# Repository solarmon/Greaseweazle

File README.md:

# Greaseweazle Projects
Greaseweazle Projects

Various PCB projects based on **keirf**'s Greaseweazle project for reading and writing floppy disks:

https://github.com/keirf/Greaseweazle

Special thanks to **Stefano Cappelli** of https://www.picoelements.com/ for making the time and effort to beta testing these boards. 

# Greaseweazle F1 Plus

## Features

These are the features of the GW F1 Plus boards.

**Standard Features:**
|   | F1 Plus Mini Rev 1.1 | F1 Plus  Rev 1.1 | F1 Plus Gotek	 Rev 1.1 | F1 Plus 3.5" Rev 1.1 |
|---|---|---|---|---|
|Jumperless Update|Yes|Yes|Yes|Yes|
|Multiple Drives|Yes|Yes|Yes|Yes|
|Write-Protect Jumper| - |Yes|Yes|Yes|
|Buffered Outputs| - |Yes|Yes|Yes|
|High-Speed USB| - | - | - | - |			
|12v Power| - |Yes|Yes|Yes|
|Flippy Drive| - |Yes|Yes|Yes|
|Disk Change Detect|Yes|Yes|Yes|Yes|
|User Outputs|3|3|3|3|

Note: **Disk Change Detect** allows WinUAE integration - see https://amiga.robsmithdev.co.uk/winuae

The features of the official Greaseweazle models can be seen at:

https://github.com/keirf/Greaseweazle/wiki/Greaseweazle-Models

**Other Features:**
|   | F1 Plus Mini Rev 1.1 | F1 Plus  Rev 1.1 | F1 Plus Gotek	 Rev 1.1 | F1 Plus 3.5" Rev 1.1 |
|---|---|---|---|---|
|Gotek Case Form Factor| - | -  |Yes|		-		|
|3.5" Floppy Drive Form Factor| - | - |		-		|			Yes|
|STM32 Blue Pill MCU|Yes|Yes|Yes|Yes|
|**Arduino Nano Track Display:**| - | - |		Yes|				Yes|
|	- LEDC68 Display| - | - |			Yes|				Yes|
|	- 0.91" OLED Display| - | - |		(Yes)|			Yes|
|	- 0.96" OLED Display| - | - |		(Yes)|			Yes|
|	- SD Card Reader| - | - |			Yes|				Yes|
|USB ESD Protection| - | (Yes) |				Yes|				Yes|
|12V Reverse Polarity Protection| - | Yes |	Yes|				Yes|
|Poly Fuse| - |Yes|						Yes|				Yes|
|**LED Status:**|Yes|Yes|						Yes|				Yes|
|	- Activity|Yes|Yes|					Yes|				Yes|
|	- 3.3V|Yes|Yes|						Yes|				Yes|
|	- 5V|Yes|Yes|							Yes|				Yes|
|	- 12V| - |Yes |							Yes|				Yes|
| - Type: SMT|Yes|Yes| - | Yes|
| - Type: THT|Yes|Yes| Yes | Yes|
|**Power Jumpers:**|Yes|Yes|						Yes|				Yes|
|	- 12V|-|Yes|Yes|Yes|
|	- 5V|Yes|Yes|Yes|Yes|
|Write Enable Jumper| - |Yes|				Yes|				Yes|
|Input pullups|Yes|Yes|					Yes|				Yes|
|Reset Button|Yes|Yes|					Yes|				Yes|
|Serial Programming Header|Yes|Yes|		Yes|				Yes|
|SWD Programming Header|-|Yes|			Yes|				Yes|
|Disk Change Jumper|Yes|Yes|Yes|Yes|

**Note:** The **Disk Change Jumper** allows you to use an Amiga drive with WinUAE.

## Greaseweazle F1 Plus Mini Rev 1.1

**Design Files:** https://github.com/solarmon/Greaseweazle/tree/main/Greaseweazle%20F1%20Plus%20Mini%20Rev%201.1

This is the most basic F1 Plus model and has the smallest footprint.

## Greaseweazle F1 Plus Rev 1.1

**Design Files:** https://github.com/solarmon/Greaseweazle/tree/main/Greaseweazle%20F1%20Plus%20Rev%201.1

This is the standard F1 Plus model, has a standard footprint but no Track Display features. 

## Greaseweazle F1 Plus Gotek

**Design Files:** https://github.com/solarmon/Greaseweazle/tree/main/Greaseweazle%20F1%20Plus%20Gotek%20Rev%201.1

This Greaseweazle board has been designed to re-purpose and fit into an original Gotek case; and to make use of its LEDC68 display as a track display.

It has been designed to sit on top of the floppy drive that is connected to it.

## Greaseweazle F1 Plus 3.5"

**Design Files:** https://github.com/solarmon/Greaseweazle/tree/main/Greaseweazle%20F1%20Plus%203.5%20Rev%201.1

This Greaseweazle board has been designed to have a 3.5" floppy drive mounted directly on top of it, using the floppy drive standard mounting holes.

The track display feature can support the LEDC68 Gotek LED display, or a 128x32 0.91" OLED display, or a 128x64 0.96" OLED display.

## Track Display

The GW F1 Plus Gotek/3.5" Track Display is provided by an Arduino Nano. The Arduino sketch for this can be found at:

https://github.com/solarmon/Greaseweazle/tree/main/Arduino_Nano_GW_F1_Plus_Floppy_Drive_Track_Display_LED_and_OLED

The LEDC68 and OLED display adapter board, used in the GW F1 3.5" and GW F1 Plus 3.5" boards, can be found at:

https://github.com/solarmon/Greaseweazle/tree/main/LEDC68%20and%200.9%20Inch%20OLED%20Adapter

# Older Revisions

Design files for older revisions of the GW F1 boards can be found at:

## GW F1 Plus Mini

* Rev 1: https://github.com/solarmon/Greaseweazle/tree/main/Greaseweazle%20F1%20Plus%20Mini
 
## GW F1 Plus

* Rev 1: https://github.com/solarmon/Greaseweazle/tree/main/Greaseweazle%20F1%20Plus

## GW F1 Plus Gotek

* Rev 1: https://github.com/solarmon/Greaseweazle/tree/main/Greaseweazle%20F1%20Plus%20Gotek

## GW F1 Plus 3.5"

* Rev 1: https://github.com/solarmon/Greaseweazle/tree/main/Greaseweazle%20F1%20Plus%203.5

## GW F1 Gotek

* Rev 1 (USB-B): https://github.com/solarmon/Greaseweazle/tree/main/Greaseweazle%20F1%20in%20a%20Gotek%20Case%20(%2B%20USB%20B)
* Rev 1 (USB-A): https://github.com/solarmon/Greaseweazle/tree/main/Greaseweazle%20F1%20in%20a%20Gotek%20Case%20(USB-A)
* Rev 2: https://github.com/solarmon/Greaseweazle/tree/main/Greaseweazle%20F1%20Gotek%20Rev%202
* Rev 2B: https://github.com/solarmon/Greaseweazle/tree/main/Greaseweazle%20F1%20Gotek%20Rev%202B

## GW F1 3.5"

* Rev 1: https://github.com/solarmon/Greaseweazle/tree/main/Greaseweazle%20F1%203.5%20Inch
* Rev 2: https://github.com/solarmon/Greaseweazle/tree/main/Greaseweazle%20F1%203.5%20Inch%20Rev%202
* Rev 2B: https://github.com/solarmon/Greaseweazle/tree/main/Greaseweazle%20F1%203.5%20Inch%20Rev%202B

## Track Display

These older revision GW F1 Plus Track Display is provided by an Arduino Nano. The Arduino sketch for this can be found at:

https://github.com/solarmon/Greaseweazle/tree/main/Arduino_Nano_GW_F1_Floppy_Drive_Track_Display_LED_and_OLED_v1

The LEDC68 and OLED display adapter board can be found at:

https://github.com/solarmon/Greaseweazle/tree/main/LEDC68%20and%200.9%20Inch%20OLED%20Adapter

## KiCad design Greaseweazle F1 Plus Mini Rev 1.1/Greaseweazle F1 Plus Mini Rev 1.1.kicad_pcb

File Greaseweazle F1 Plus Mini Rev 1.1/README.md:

# Greaseweazle F1 Plus Mini

This is the most basic F1 Plus model and has the smallest footprint.

## Jumpers

* **JP101** - Disk Change
  - **Pin 34** (Default) - For PC drives
  - **Pin 2** - For Amiga drives

* **JP102** - Join S0/B
  - If **JP101** set to **Pin 2** then set JP102 to join S0 with B

To use an **Amiga** floppy drive with WinUAE, jumper **JP101** to **Pin 2** and jumper **JP102**. An Amiga drive set to S0 will be usable in WinuAE as drive B.

## Headers

* **JP5** - Reset

* **CN4** - USB Header

* **CN5** - Serial Port

* **DH2** - +5V LED
* **DH3** - +3V3 LED
* **DH4** - ACT LED

## Connectors

* **CN1** - Floppy Data
* **CN2** - Floppy Power (Out)
* **CN3** - USB B
* **CN6** - Floppy Power (In)

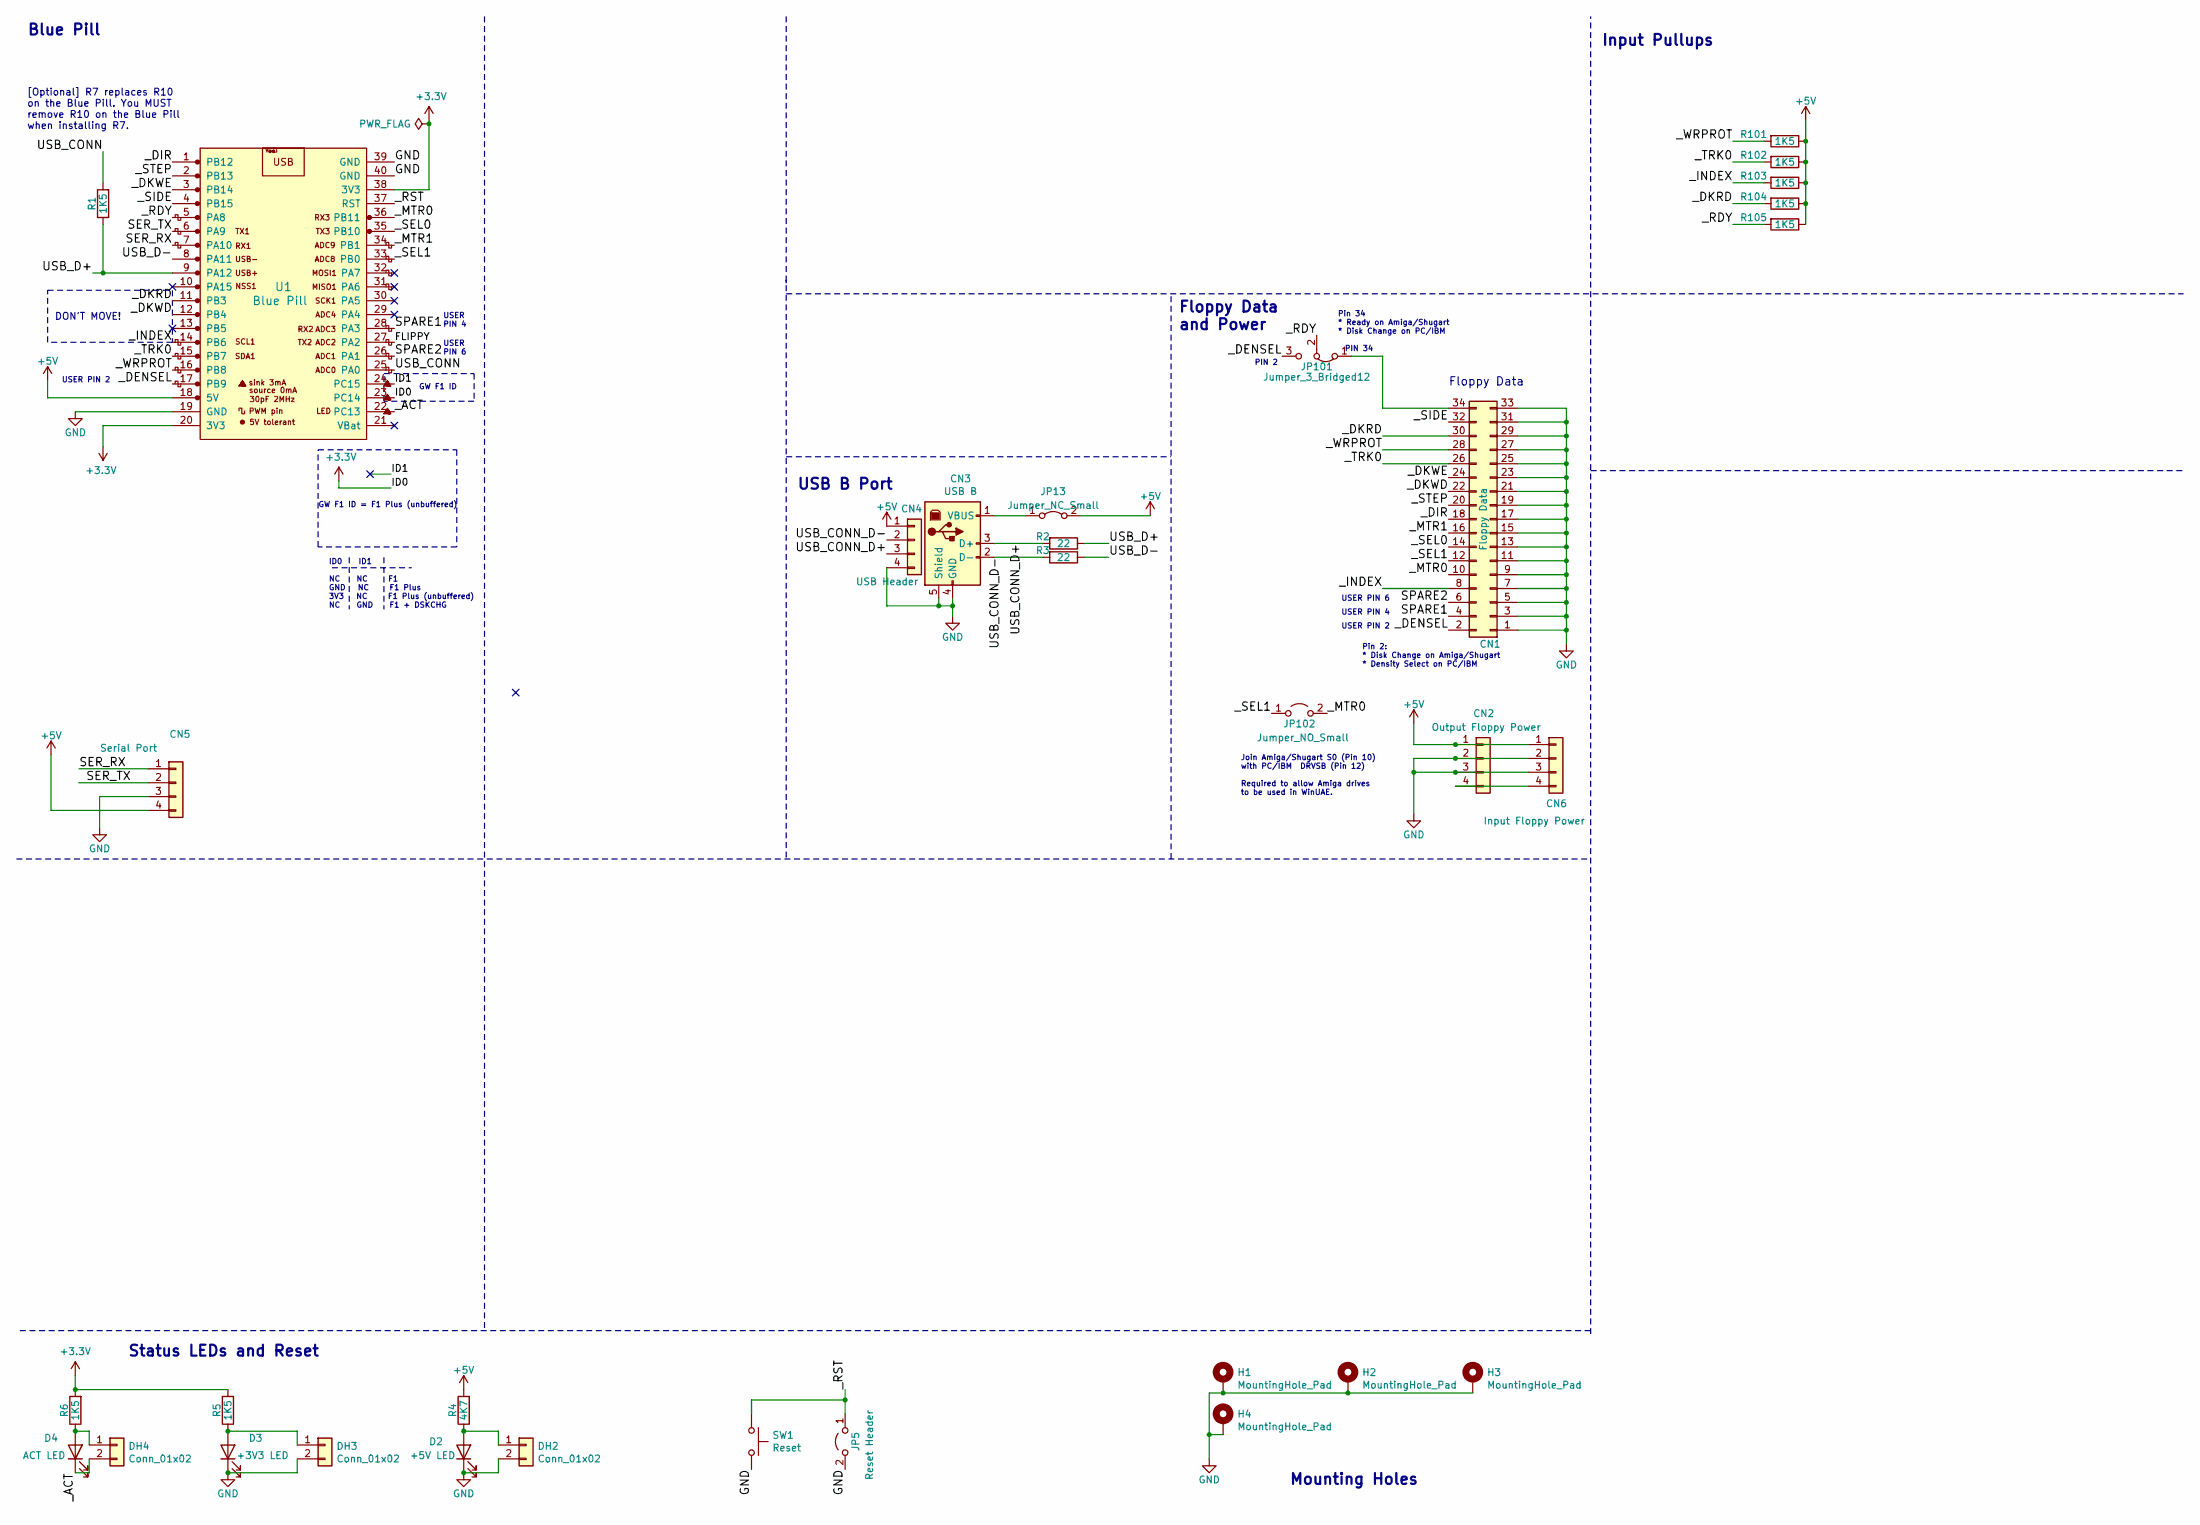
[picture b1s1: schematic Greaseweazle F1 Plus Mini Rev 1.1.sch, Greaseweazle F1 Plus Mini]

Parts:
CN1: Floppy Data; PinHeader_2x17_P2.54mm_Vertical
CN2: Output Floppy Power; PinHeader_1x04_P2.54mm_Horizontal
CN3: USB B; conn_usb_B; LCSC C498173
CN4: USB Header; PinHeader_1x04_P2.54mm_Vertical
CN5: Serial Port; PinHeader_1x04_P2.54mm_Vertical
CN6: Input Floppy Power; PinHeader_1x04_P2.54mm_Vertical
D2: +5V LED; LED_0805_2012Metric_Pad1.15x1.40mm_HandSolder
D3: +3V3 LED; LED_0805_2012Metric_Pad1.15x1.40mm_HandSolder
D4: ACT LED; LED_0805_2012Metric_Pad1.15x1.40mm_HandSolder
DH2, DH3, DH4: Conn_01x02; PinHeader_1x02_P2.54mm_Vertical
H1, H2, H3, H4: MountingHole_Pad; HOLE_3MM
JP5: Reset Header; PinHeader_1x02_P2.54mm_Vertical
JP13: Jumper_NC_Small; PinHeader_1x02_P2.54mm_Vertical
JP101: Jumper_3_Bridged12; PinHeader_1x03_P2.54mm_Vertical
JP102: Jumper_NO_Small; PinHeader_1x02_P2.54mm_Vertical
R1, R101, R102, R103, R104, R105: 1K5; R_0805_2012Metric
R2, R3: 22; R_0805_2012Metric
R4: 4K7; R_0805_2012Metric_Pad1.20x1.40mm_HandSolder
R5, R6: 1K5; R_0805_2012Metric_Pad1.20x1.40mm_HandSolder
SW1: Reset; SW_Tactile_SPST_Angled_PTS645Vx83-2LFS
U1: Blue Pill; YAAJ_BluePill_1

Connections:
+3V3: R5.2, R6.2, U1.20 (3V3), U1.23 (PC14), U1.38 (3V3)
+5V: CN2.1, CN4.1, CN5.4, CN6.1, JP13.2 (B), R4.2, R101.1, R102.1, R103.1, R104.1, R105.1, U1.18 (5V)
/FLIPPY: U1.27 (PA2)
/ID1: U1.24 (PC15)
/SER_RX: CN5.1, U1.7 (PA10)
/SER_TX: CN5.2, U1.6 (PA9)
/SPARE1: CN1.4, U1.28 (PA3)
/SPARE2: CN1.6, U1.26 (PA1)
/USB_CONN: R1.2, U1.25 (PA0)
/USB_CONN_D+: CN3.3 (D+), CN4.3, R2.2
/USB_CONN_D-: CN3.2 (D-), CN4.2, R3.2
/USB_D+: R1.1, R2.1, U1.9 (PA12)
/USB_D-: R3.1, U1.8 (PA11)
/_ACT: D4.1 (K), DH4.2, U1.22 (PC13)
/_DENSEL: CN1.2, JP101.3 (B), U1.17 (PB9)
/_DIR: CN1.18, U1.1 (PB12)
/_DKRD: CN1.30, R104.2, U1.11 (PB3)
/_DKWD: CN1.22, U1.12 (PB4)
/_DKWE: CN1.24, U1.3 (PB14)
/_INDEX: CN1.8, R103.2, U1.14 (PB6)
/_MTR0: CN1.10, JP102.2 (B), U1.36 (PB11)
/_MTR1: CN1.16, U1.34 (PB1)
/_RDY: JP101.2 (C), R105.2, U1.5 (PA8)
/_RST: JP5.1 (A), SW1.1, U1.37 (RST)
/_SEL0: CN1.14, U1.35 (PB10)
/_SEL1: CN1.12, JP102.1 (A), U1.33 (PB0)
/_SIDE: CN1.32, U1.4 (PB15)
/_STEP: CN1.20, U1.2 (PB13)
/_TRK0: CN1.26, R102.2, U1.15 (PB7)
/_WRPROT: CN1.28, R101.2, U1.16 (PB8)
GND: CN1.1, CN1.3, CN1.5, CN1.7, CN1.9, CN1.11, CN1.13, CN1.15, CN1.17, CN1.19, CN1.21, CN1.23, CN1.25, CN1.27, CN1.29, CN1.31, CN1.33, CN2.2, CN2.3, CN3.4 (GND), CN3.5 (Shield), CN4.4, CN5.3, CN6.2, CN6.3, D2.1 (K), D3.1 (K), DH2.2, DH3.2, H1.1, H2.1, H3.1, H4.1, JP5.2 (B), SW1.2, U1.19 (GND), U1.39 (GND), U1.40 (GND)
unnamed: CN1.34, JP101.1 (A)
unnamed: CN2.4, CN6.4
unnamed: CN3.1 (VBUS), JP13.1 (A)
unnamed: D2.2 (A), DH2.1, R4.1
unnamed: D3.2 (A), DH3.1, R5.1
unnamed: D4.2 (A), DH4.1, R6.1

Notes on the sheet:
Floppy Data
[Optional] R7 replaces R10 on the Blue Pill. You MUST remove R10 on the Blue Pill when installing R7.
USB B Port
Floppy Data and Power
Blue Pill
Status LEDs and Reset
Mounting Holes
GW F1 ID = F1 Plus (unbuffered)
GW F1 ID
DON'T MOVE!
Input Pullups
USER PIN 2
USER PIN 4
USER PIN 6
USER PIN 4
USER PIN 6
Pin 34 * Ready on Amiga/Shugart * Disk Change on PC/IBM
ID0 ID1 NC NC F1 GND NC F1 Plus 3V3 NC F1 Plus (unbuffered) NC GND F1 + DSKCHG
Pin 2: * Disk Change on Amiga/Shugart * Density Select on PC/IBM
Join Amiga/Shugart S0 (Pin 10) with PC/IBM DRVSB (Pin 12) Required to allow Amiga drives to be used in WinUAE.
PIN 2
PIN 34

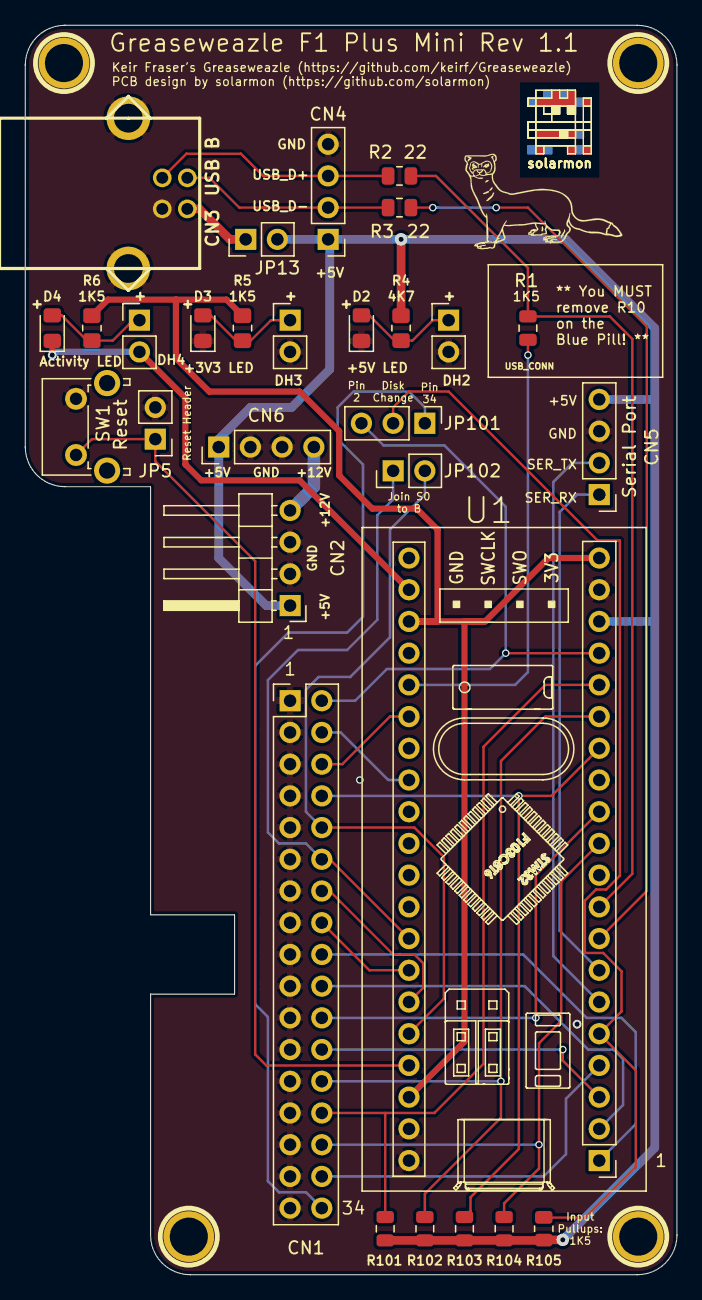
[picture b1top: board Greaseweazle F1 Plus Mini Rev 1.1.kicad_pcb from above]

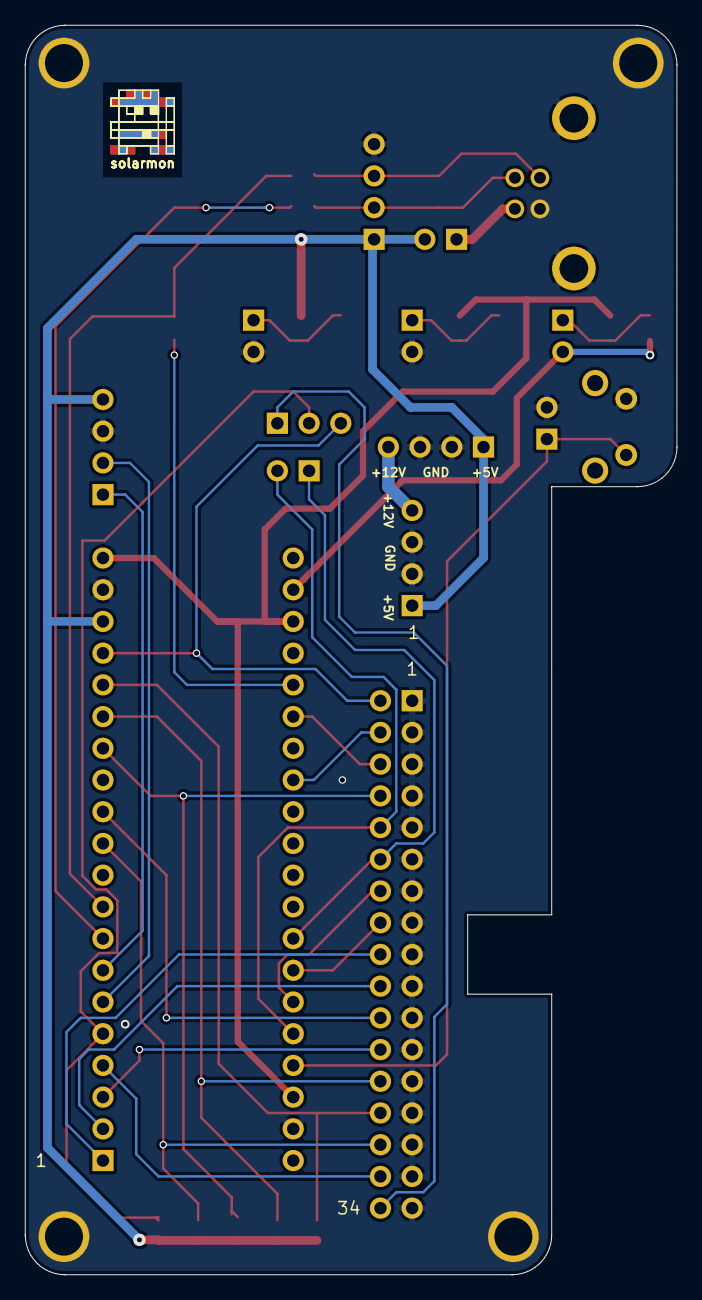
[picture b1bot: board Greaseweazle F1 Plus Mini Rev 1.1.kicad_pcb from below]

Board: 2 copper layers, 52.2 x 100.1 mm, 38 parts (2 on the bottom side), 35 nets.

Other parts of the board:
G**: Weasle; WeasleLogo
solarmon: solarmon-logo-25mils
solarmon#2, solarmon#3, solarmon#4: solarmon-logo-25mils

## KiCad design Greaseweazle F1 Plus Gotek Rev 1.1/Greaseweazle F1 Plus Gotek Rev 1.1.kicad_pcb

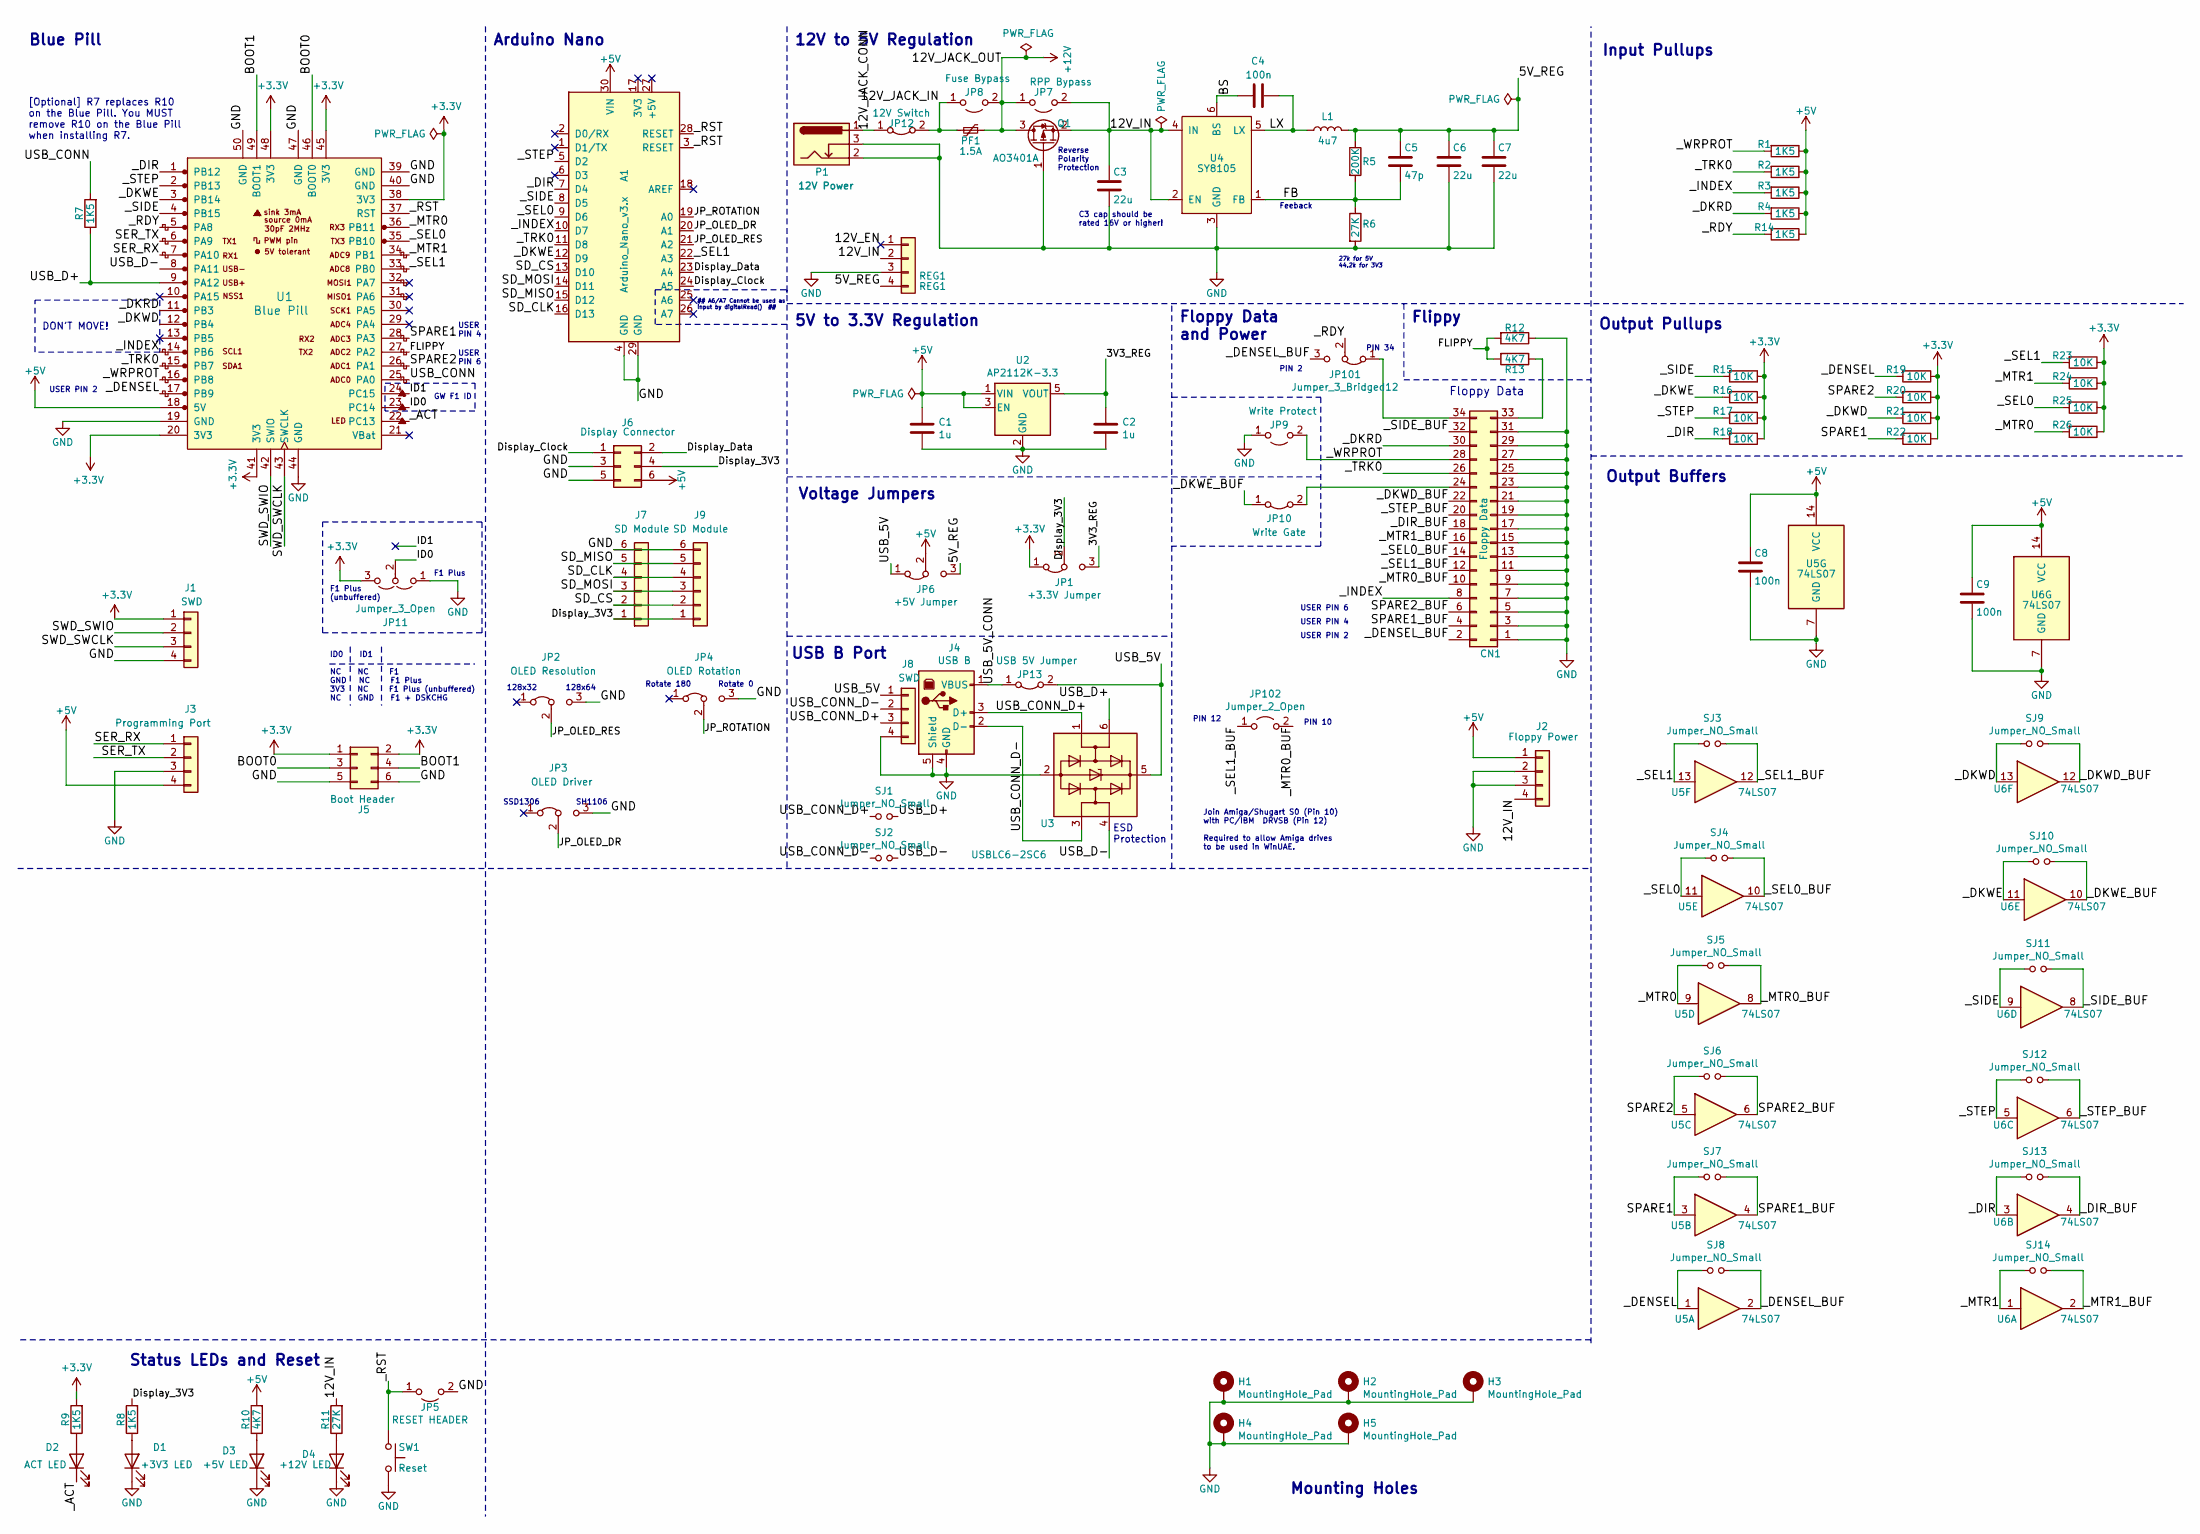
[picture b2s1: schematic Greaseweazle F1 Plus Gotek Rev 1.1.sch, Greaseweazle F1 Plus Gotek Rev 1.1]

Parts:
A1: Arduino_Nano_v3.x; Arduino_Nano
C1, C2: 1u; C_0805_2012Metric_Pad1.15x1.40mm_HandSolder
C3, C6, C7: 22u; C_0805_2012Metric_Pad1.15x1.40mm_HandSolder
C4, C8, C9: 100n; C_0805_2012Metric_Pad1.15x1.40mm_HandSolder
C5: 47p; C_0805_2012Metric_Pad1.15x1.40mm_HandSolder
CN1: Floppy Data; PinHeader_2x17_P2.54mm_Vertical
D1: +3V3 LED; LED_D3.0mm_Horizontal_O6.35mm_Z10.0mm
D2: ACT LED; LED_D3.0mm_Horizontal_O6.35mm_Z10.0mm
D3: +5V LED; LED_D3.0mm_Horizontal_O3.81mm_Z6.0mm
D4: +12V LED; LED_D3.0mm_Horizontal_O3.81mm_Z6.0mm
H1, H2, H3, H4, H5: MountingHole_Pad; MountingHole_M3_Pad
J1, J8: SWD; PinHeader_1x04_P2.54mm_Vertical
J2: Floppy Power; PinHeader_1x04_P2.54mm_Horizontal
J3: Programming Port; PinHeader_1x04_P2.54mm_Horizontal
J4: USB B; conn_usb_B; LCSC C498173
J5: Boot Header; PinHeader_2x03_P2.54mm_Vertical
J6: Display Connector; PinHeader_2x03_P2.54mm_Horizontal
J7, J9: SD Module; SD_Micro_Module_Upside_Down
JP1: +3.3V Jumper; PinHeader_1x03_P2.54mm_Vertical
JP2: OLED Resolution; PinHeader_1x03_P2.54mm_Vertical
JP3: OLED Driver; PinHeader_1x03_P2.54mm_Vertical
JP4: OLED Rotation; PinHeader_1x03_P2.54mm_Vertical
JP5: RESET HEADER; PinHeader_1x02_P2.54mm_Vertical
JP6: +5V Jumper; PinHeader_1x03_P2.54mm_Vertical
JP7: RPP Bypass; PinHeader_1x02_P2.54mm_Vertical
JP8: Fuse Bypass; PinHeader_1x02_P2.54mm_Vertical
JP9: Write Protect; PinHeader_1x02_P2.54mm_Vertical
JP10: Write Gate; PinHeader_1x02_P2.54mm_Vertical
JP11: Jumper_3_Open; SolderJumper-3_P1.3mm_Open_RoundedPad1.0x1.5mm
JP12: 12V Switch; PinHeader_1x02_P2.54mm_Vertical
JP13: USB 5V Jumper; PinHeader_1x02_P2.54mm_Vertical
JP101: Jumper_3_Bridged12; PinHeader_1x03_P2.54mm_Vertical
JP102: Jumper_2_Open; PinHeader_1x02_P2.54mm_Vertical
L1: 4u7; MWSA0503S; LCSC C408410
P1: 12V Power; BarrelJack_Horizontal; LCSC C16214
PF1: 1.5A; Fuse_1206_3216Metric_Pad1.42x1.75mm_HandSolder; LCSC C371166
Q1: AO3401A; SOT-23_Handsoldering; LCSC C15127
R1, R2, R3, R4, R7, R8, R9, R14: 1K5; R_0805_2012Metric
R5: 200K; R_0805_2012Metric
R6, R11: 27K; R_0805_2012Metric
R10, R12, R13: 4K7; R_0805_2012Metric
R15, R16, R17, R18, R19, R20, R21, R22, R23, R24, R25, R26: 10K; R_0805_2012Metric
REG1: REG1; PinHeader_1x04_P2.54mm_Vertical
SJ1, SJ2, SJ3, SJ4, SJ5, SJ6, SJ7, SJ8, SJ9, SJ10, SJ11, SJ12, SJ13, SJ14: Jumper_NO_Small; SolderJumper-2_Open_RoundedPad0.5x1.0mm
SW1: Reset; PUSH_BUTTON_RIGHT_ANGLE
U1: Blue Pill; YAAJ_BluePill_SWD_1_BootPins
U2: AP2112K-3.3; SOT-23-5_HandSoldering; LCSC C51118
U3: USBLC6-2SC6; SOT-23-6_Handsoldering; LCSC C7519
U4: SY8105; TSOT-23-6_HandSoldering; LCSC C178247
U5, U6: 74LS07; SOIC-14_3.9x8.7mm_P1.27mm; LCSC C513513

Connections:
+3V3: J1.1, J5.1, J5.2, JP1.1 (A), JP11.3 (B), R9.2, R15.1, R16.1, R17.1, R18.1, R19.1, R20.1, R21.1, R22.1, R23.1, R24.1, R25.1, R26.1, U1.20 (3V3), U1.38 (3V3), U1.41 (3V3), U1.45 (3V3), U1.48 (3V3); also elsewhere on the board
+5V: A1.30 (VIN), C1.1, C8.1, C9.1, J2.1, J3.4, J6.6, JP6.2 (C), R1.1, R2.1, R3.1, R4.1, R10.2, R14.1, U1.18 (5V), U2.1 (VIN), U2.3 (EN), U5.14 (VCC), U6.14 (VCC); also elsewhere on the board
+12V: JP7.1 (A), JP8.2 (B), PF1.1, Q1.3 (D)
/3V3_REG: C2.1, JP1.3 (B), U2.5 (VOUT)
/5V_REG: C5.1, C6.1, C7.1, JP6.3 (B), L1.2, R5.1, REG1.4
/12V_EN: REG1.1
/12V_JACK_CONN: JP12.1 (A), P1.1
/12V_JACK_IN: JP8.1 (A), JP12.2 (B), PF1.2
/BOOT0: J5.3, U1.46 (BOOT0)
/BOOT1: J5.4, U1.49 (BOOT1)
/BS: C4.1, U4.6 (BS)
/Display_3V3: J6.4, J7.1, J9.1, JP1.2 (C), R8.2; also elsewhere on the board
/Display_Clock: A1.24 (A5), J6.1
/Display_Data: A1.23 (A4), J6.2
/FB: C5.2, R5.2, R6.1, U4.1 (FB)
/FLIPPY: R12.2, R13.2, U1.27 (PA2)
/ID0: JP11.2 (C), U1.23 (PC14)
/ID1: U1.24 (PC15)
/JP_OLED_DR: A1.20 (A1), JP3.2 (C)
/JP_OLED_RES: A1.21 (A2), JP2.2 (C)
/JP_ROTATION: A1.19 (A0), JP4.2 (C)
/LX: C4.2, L1.1, U4.5 (LX)
/SD_CLK: A1.16 (D13), J7.4, J9.4
/SD_CS: A1.13 (D10), J7.2, J9.2
/SD_MISO: A1.15 (D12), J7.5, J9.5
/SD_MOSI: A1.14 (D11), J7.3, J9.3
/SER_RX: J3.1, U1.7 (PA10)
/SER_TX: J3.2, U1.6 (PA9)
/SPARE1: R22.2, SJ7.1, U1.28 (PA3), U5.3
/SPARE1_BUF: CN1.4, SJ7.2, U5.4
/SPARE2: R20.2, SJ6.1, U1.26 (PA1), U5.5
/SPARE2_BUF: CN1.6, SJ6.2, U5.6
/SWD_SWCLK: J1.3, U1.43 (SWCLK)
/SWD_SWIO: J1.2, U1.42 (SWIO)
/USB_5V: J8.1, JP6.1 (A), JP13.2 (B), U3.5 (VBUS)
/USB_5V_CONN: J4.1 (VBUS), JP13.1 (A)
/USB_CONN: R7.2, U1.25 (PA0)
/USB_CONN_D+: J4.3 (D+), J8.3, SJ1.1, U3.1 (I/O1)
/USB_CONN_D-: J4.2 (D-), J8.2, SJ2.1, U3.3 (I/O2)
/USB_D+: R7.1, SJ1.2, U1.9 (PA12), U3.6 (I/O1)
/USB_D-: SJ2.2, U1.8 (PA11), U3.4 (I/O2)
/_ACT: D2.1 (K), U1.22 (PC13)
/_DENSEL: R19.2, SJ8.1, U1.17 (PB9), U5.1
/_DENSEL_BUF: CN1.2, JP101.3 (B), SJ8.2, U5.2
/_DIR: A1.7 (D4), R18.2, SJ13.1, U1.1 (PB12), U6.3
/_DIR_BUF: CN1.18, SJ13.2, U6.4
/_DKRD: CN1.30, R4.2, U1.11 (PB3)
/_DKWD: R21.2, SJ9.1, U1.12 (PB4), U6.13
/_DKWD_BUF: CN1.22, SJ9.2, U6.12
/_DKWE: A1.12 (D9), R16.2, SJ10.1, U1.3 (PB14), U6.11
/_DKWE_BUF: JP10.1 (A), SJ10.2, U6.10
/_INDEX: A1.10 (D7), CN1.8, R3.2, U1.14 (PB6)
/_MTR0: R26.2, SJ5.1, U1.36 (PB11), U5.9
/_MTR0_BUF: CN1.10, JP102.2 (B), SJ5.2, U5.8
/_MTR1: R24.2, SJ14.1, U1.34 (PB1), U6.1
/_MTR1_BUF: CN1.16, SJ14.2, U6.2
/_RDY: JP101.2 (C), R14.2, U1.5 (PA8)
/_RST: A1.3 (RESET), A1.28 (RESET), JP5.1 (A), SW1.1, U1.37 (RST)
/_SEL0: A1.9 (D6), R25.2, SJ4.1, U1.35 (PB10), U5.11
/_SEL0_BUF: CN1.14, SJ4.2, U5.10
/_SEL1: A1.22 (A3), R23.2, SJ3.1, U1.33 (PB0), U5.13
/_SEL1_BUF: CN1.12, JP102.1 (A), SJ3.2, U5.12
/_SIDE: A1.8 (D5), R15.2, SJ11.1, U1.4 (PB15), U6.9
/_SIDE_BUF: CN1.32, SJ11.2, U6.8
/_STEP: A1.5 (D2), R17.2, SJ12.1, U1.2 (PB13), U6.5
/_STEP_BUF: CN1.20, SJ12.2, U6.6
/_TRK0: A1.11 (D8), CN1.26, R2.2, U1.15 (PB7)
/_WRPROT: CN1.28, JP9.2 (B), R1.2, U1.16 (PB8)
GND: A1.4 (GND), A1.29 (GND), C1.2, C2.2, C3.2, C6.2, C7.2, C8.2, C9.2, CN1.1, CN1.3, CN1.5, CN1.7, CN1.9, CN1.11, CN1.13, CN1.15, CN1.17, CN1.19, CN1.21, CN1.23, CN1.25, CN1.27, CN1.29, CN1.31, D1.1 (K), D3.1 (K), D4.1 (K), H1.1, H2.1, H3.1, H4.1, H5.1, J1.4, J2.2, J2.3, J3.3, J4.4 (GND), J4.5 (Shield), J5.5, J5.6, J6.3, J6.5, J7.6, J8.4, J9.6, JP2.3 (B), JP3.3 (B), JP4.3 (B), JP5.2 (B), JP9.1 (A), JP11.1 (A), P1.2, P1.3, Q1.1 (G), R6.2, R12.1, REG1.3, SW1.2, U1.19 (GND), U1.39 (GND), U1.40 (GND), U1.44 (GND), U1.47 (GND), U1.50 (GND), U2.2 (GND), U3.2 (GND), U4.3 (GND), U5.7 (GND), U6.7 (GND); also elsewhere on the board
unnamed: CN1.24, JP10.2 (B)
unnamed: CN1.33, R13.1
unnamed: CN1.34, JP101.1 (A)
unnamed 80: D1.2 (A), R8.1; also elsewhere on the board
unnamed 81: D2.2 (A), R9.1; also elsewhere on the board
unnamed 82: D3.2 (A), R10.1; also elsewhere on the board

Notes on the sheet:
Floppy Data
[Optional] R7 replaces R10 on the Blue Pill. You MUST remove R10 on the Blue Pill when installing R7.
12V to 5V Regulation
5V to 3.3V Regulation
Voltage Jumpers
USB B Port
Floppy Data and Power
Arduino Nano
Blue Pill
Status LEDs and Reset
Reverse Polarity Protection
27k for 5V 44.2k for 3V3
Mounting Holes
Rotate 180
Rotate 0
128x64
SSD1306
SH1106
128x32
Feeback
C3 cap should be rated 16V or higher!
F1 Plus
GW F1 ID
DON'T MOVE!
ESD Protection
Output Pullups
Output Buffers
Input Pullups
Flippy
## A6/A7 Cannot be used as input by digitalRead() ##
USER PIN 2
USER PIN 4
USER PIN 6
USER PIN 4
USER PIN 6
PIN 10
PIN 12
Join Amiga/Shugart S0 (Pin 10) with PC/IBM DRVSB (Pin 12) Required to allow Amiga drives to be used in WinUAE.
PIN 34
PIN 2

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
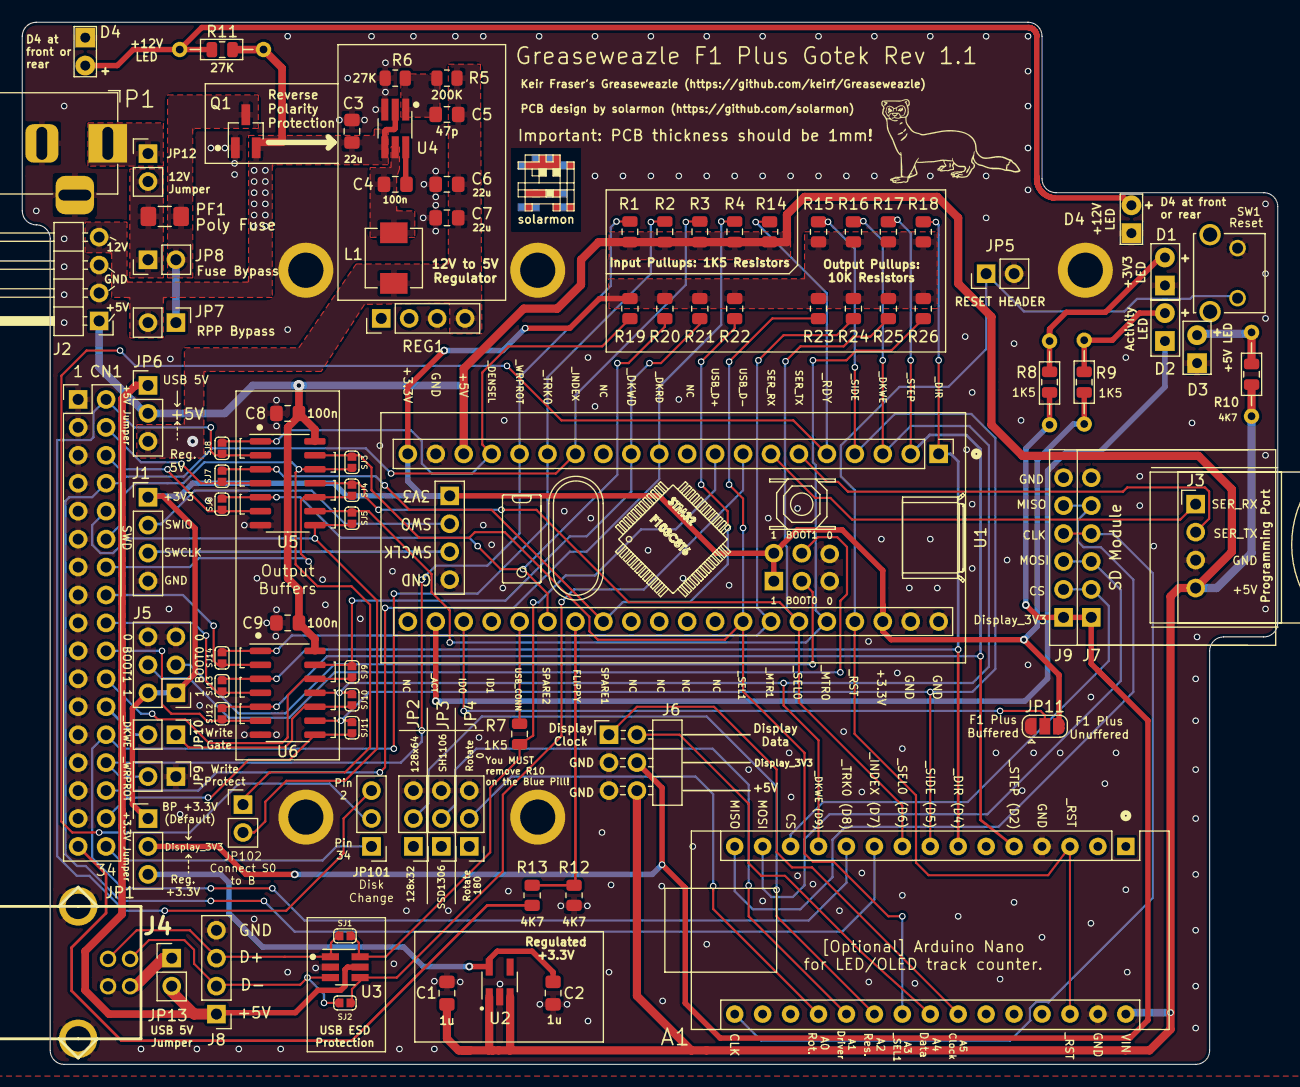
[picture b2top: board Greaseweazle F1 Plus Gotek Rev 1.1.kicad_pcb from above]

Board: 2 copper layers, 114.1 x 94.7 mm, 104 parts (1 on the bottom side), 75 nets.

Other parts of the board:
D4#2: +12V LED; LED_D3.0mm_Horizontal_O3.81mm_Z6.0mm
G**: Weasle; WeasleLogo
R8#2, R9#2: 1K5; R_0805_2012Metric
R10#2: 4K7; R_0805_2012Metric
R11#2: 27K; R_0805_2012Metric
solarmon: solarmon-logo-25mils
solarmon#2: solarmon-logo-25mils

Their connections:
+3V3: R9#2.2; also elsewhere on the board
+5V: R10#2.2; also elsewhere on the board
/Display_3V3: R8#2.2; also elsewhere on the board
GND: D4#2.1; also elsewhere on the board
unnamed 80: R8#2.1; also elsewhere on the board
unnamed 81: R9#2.1; also elsewhere on the board
unnamed 82: R10#2.1; also elsewhere on the board
